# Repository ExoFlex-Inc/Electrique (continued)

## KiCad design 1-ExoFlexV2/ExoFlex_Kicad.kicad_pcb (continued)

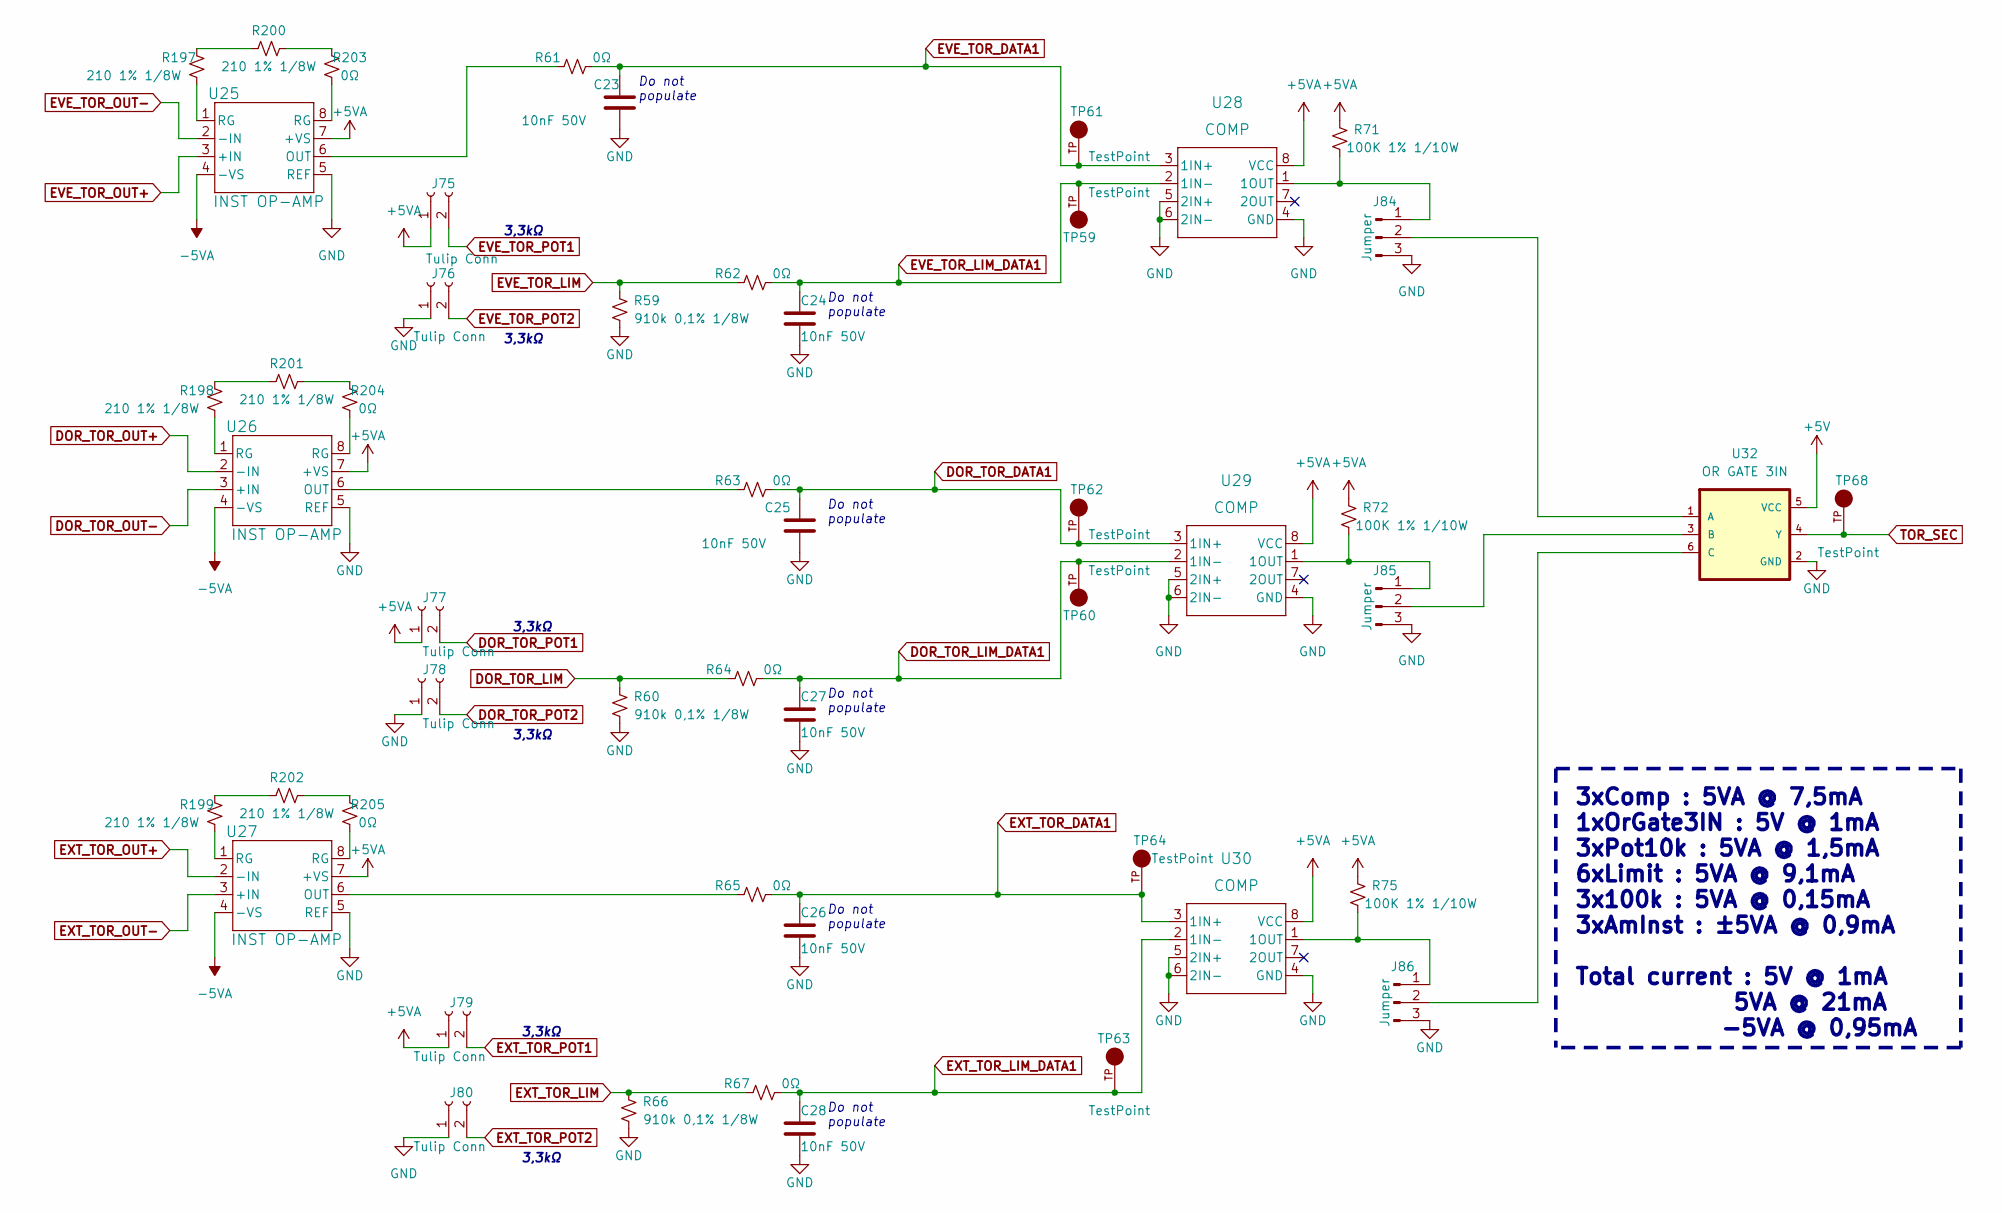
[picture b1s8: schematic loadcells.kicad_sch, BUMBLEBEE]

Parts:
C23, C24, C25, C26, C27, C28: 10nF 50V; C_0805_2012Metric; PART NUMBER GRM2195C1H103JA01D
J75, J76, J77, J78, J79, J80: Tulip Conn; PinSocket_1x02_P2.54mm_Vertical; PART NUMBER 801-87-002-10-001101
J84, J85, J86: Jumper; PinHeader_1x03_P2.54mm_Vertical; PART NUMBER 61300311121
R59, R60, R66: 910k 0,1% 1/8W; R_0805_2012Metric; PART NUMBER ERA-6AEB914V
R61, R62, R63, R64, R65, R67, R203, R204, R205: 0Ω; R_0805_2012Metric; PART NUMBER ERJ-6GEY0R00V
R71, R72, R75: 100K 1% 1/10W; R_0603_1608Metric; PART NUMBER ERJ-3EKF1003V
R197, R198, R199, R200, R201, R202: 210 1% 1/8W; R_0805_2012Metric; PART NUMBER ERJ-6ENF2100V
TP59, TP60, TP61, TP62, TP63, TP64, TP68: TestPoint; KEYSTONE_5005; PART NUMBER 5005
U25, U26, U27: INST OP-AMP; D0008A_SOIC_TEX; PART NUMBER INA823DR
U28, U29, U30: COMP; DGK8; PART NUMBER LM393DGKR
U32: OR GATE 3IN; SOT95P280X145-6N; PART NUMBER SN74LVC1G332DBVR

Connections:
+5V: U32.5 (VCC); also elsewhere on the board
+5VA: J75.1, J77.1, J79.1, R71.1, R72.1, R75.1, U25.7 (+VS), U26.7 (+VS), U27.7 (+VS), U28.8 (VCC), U29.8 (VCC), U30.8 (VCC); also elsewhere on the board
-5VA: U25.4 (-VS), U26.4 (-VS), U27.4 (-VS); also elsewhere on the board
DOR_TOR_DATA1: C25.1, R63.2, TP62.TP, U29.3 (1IN+); also elsewhere on the board
DOR_TOR_LIM: R60.1, R64.1; also elsewhere on the board
DOR_TOR_LIM_DATA1: C27.1, R64.2, TP60.TP, U29.2 (1IN-); also elsewhere on the board
DOR_TOR_OUT+: U26.2 (-IN); also elsewhere on the board
DOR_TOR_OUT-: U26.3 (+IN); also elsewhere on the board
DOR_TOR_POT1: J77.2; also elsewhere on the board
DOR_TOR_POT2: J78.2; also elsewhere on the board
EVE_TOR_DATA1: C23.1, R61.2, TP61.TP, U28.3 (1IN+); also elsewhere on the board
EVE_TOR_LIM: R59.1, R62.1; also elsewhere on the board
EVE_TOR_LIM_DATA1: C24.1, R62.2, TP59.TP, U28.2 (1IN-); also elsewhere on the board
EVE_TOR_OUT+: U25.3 (+IN); also elsewhere on the board
EVE_TOR_OUT-: U25.2 (-IN); also elsewhere on the board
EVE_TOR_POT1: J75.2; also elsewhere on the board
EVE_TOR_POT2: J76.2; also elsewhere on the board
EXT_TOR_DATA1: C26.1, R65.2, TP64.TP, U30.3 (1IN+); also elsewhere on the board
EXT_TOR_LIM: R66.1, R67.1; also elsewhere on the board
EXT_TOR_LIM_DATA1: C28.1, R67.2, TP63.TP, U30.2 (1IN-); also elsewhere on the board
EXT_TOR_OUT+: U27.2 (-IN); also elsewhere on the board
EXT_TOR_OUT-: U27.3 (+IN); also elsewhere on the board
EXT_TOR_POT1: J79.2; also elsewhere on the board
EXT_TOR_POT2: J80.2; also elsewhere on the board
GND: C23.2, C24.2, C25.2, C26.2, C27.2, C28.2, J76.1, J78.1, J80.1, J84.3, J85.3, J86.3, R59.2, R60.2, R66.2, U25.5 (REF), U26.5 (REF), U27.5 (REF), U28.4 (GND), U28.5 (2IN+), U28.6 (2IN-), U29.4 (GND), U29.5 (2IN+), U29.6 (2IN-), U30.4 (GND), U30.5 (2IN+), U30.6 (2IN-), U32.2 (GND); also elsewhere on the board
unnamed: J84.1, R71.2, U28.1 (1OUT)
unnamed: J84.2, U32.1 (A)
unnamed: J85.1, R72.2, U29.1 (1OUT)
unnamed: J85.2, U32.3 (B)
unnamed: J86.1, R75.2, U30.1 (1OUT)
unnamed: J86.2, U32.6 (C)
unnamed: R61.1, U25.6 (OUT)
unnamed: R63.1, U26.6 (OUT)
unnamed: R65.1, U27.6 (OUT)
unnamed: R197.1, U25.1 (RG)
unnamed: R197.2, R200.1
unnamed: R198.1, U26.1 (RG)
unnamed: R198.2, R201.1
unnamed: R199.1, U27.1 (RG)
unnamed: R199.2, R202.1
unnamed: R200.2, R203.1
unnamed: R201.2, R204.1
unnamed: R202.2, R205.1
unnamed: R203.2, U25.8 (RG)
unnamed: R204.2, U26.8 (RG)
unnamed: R205.2, U27.8 (RG)
TOR_SEC: TP68.TP, U32.4 (Y); also elsewhere on the board

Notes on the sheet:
3,3kΩ
Do not populate
3xComp : 5VA @ 7,5mA 1xOrGate3IN : 5V @ 1mA 3xPot10k : 5VA @ 1,5mA 6xLimit : 5VA @ 9,1mA 3x100k : 5VA @ 0,15mA 3xAmInst : ±5VA @ 0,9mA Total current : 5V @ 1mA 5VA @ 21mA -5VA @ 0,95mA

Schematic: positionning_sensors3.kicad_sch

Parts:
C50, C51, C52: 10nF 50V; C_0805_2012Metric; PART NUMBER GRM2195C1H103JA01D
J107, J108, J109: Jumper; PinHeader_1x03_P2.54mm_Vertical; PART NUMBER 61300311121
R155, R156, R157: 0Ω; R_0805_2012Metric; PART NUMBER ERJ-6GEY0R00V
R158, R159, R160, R161, R162, R163: 100K 1% 1/10W; R_0603_1608Metric; PART NUMBER ERJ-3EKF1003V
RV3, RV4, RV5: Trim 10k; TRIM_3362P-1-103LF; PART NUMBER 3362P-1-103LF
TP108, TP109, TP110, TP111, TP112, TP113, TP117: TestPoint; KEYSTONE_5005; PART NUMBER 5005
U58: Inverter; SN74LVC3G14DCUT; PART NUMBER SN74LVC3G14DCUT
U79, U80, U81: COMP; DGK8; PART NUMBER LM393DGKR
U82, U83: AND Gate; SOT95P270X145-5N; PART NUMBER SN74LVC1G08DBVR

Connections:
+5V: U58.8 (VCC), U82.5 (VCC), U83.5 (VCC); also elsewhere on the board
+5VA: R158.1, R159.1, R160.1, R161.2, R162.2, R163.2, RV3.2, RV4.3, RV5.3, U79.8 (VCC), U80.8 (VCC), U81.8 (VCC); also elsewhere on the board
FSR_POS1: R155.1; also elsewhere on the board
FSR_POS2: R156.1; also elsewhere on the board
FSR_POS3: R157.1; also elsewhere on the board
GND: C50.2, C51.2, C52.2, RV4.1, RV5.1, U58.3 (2A), U58.4 (GND), U58.6 (3A), U79.4 (GND), U79.5 (2IN+), U79.6 (2IN-), U80.4 (GND), U80.5 (2IN+), U80.6 (2IN-), U81.4 (GND), U81.5 (2IN+), U81.6 (2IN-), U82.3 (GND), U83.3 (GND); also elsewhere on the board
M_FSR_POS1: C50.1, R155.2, TP108.TP, U79.3 (1IN+); also elsewhere on the board
M_FSR_POS2: C51.1, R156.2, TP110.TP, U80.3 (1IN+); also elsewhere on the board
M_FSR_POS3: C52.1, R157.2, TP112.TP, U81.3 (1IN+); also elsewhere on the board
M_FSR_POS_LIM1: RV3.1, TP109.TP, U79.2 (1IN-); also elsewhere on the board
M_FSR_POS_LIM2: RV4.2, TP111.TP, U80.2 (1IN-); also elsewhere on the board
M_FSR_POS_LIM3: RV5.2, TP113.TP, U81.2 (1IN-); also elsewhere on the board
unnamed: J107.1, R158.2, U80.1 (1OUT)
unnamed: J107.2, U82.2 (B)
unnamed: J107.3, R161.1
unnamed: J108.1, R159.2, U79.1 (1OUT)
unnamed: J108.2, U82.1 (A)
unnamed: J108.3, R162.1
unnamed: J109.1, R160.2, U81.1 (1OUT)
unnamed: J109.2, U83.2 (B)
unnamed: J109.3, R163.1
unnamed: U58.1 (1A), U83.4 (Y)
unnamed: U82.4 (Y), U83.1 (A)
POS_FSR_SEC: TP117.TP, U58.7 (1Y); also elsewhere on the board

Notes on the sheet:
3xComp : 5VA @ 7,5mA 2xANDGate : 5V @ 2mA 1xNOTGte : 5V @ 1mA 3xPot10k : 5VA @ 1,5mA 6x100k : 5VA @ 0,3mA Total current : 5V @ 3,15mA 5VA @ 10mA
Do not populate

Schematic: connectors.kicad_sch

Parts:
D3, D4, D7, D8, D11, D13, D14, D17, D19, D21, D22, D23, D24, D25, D26, D27, D28, D29, D30, D31, D32, D33, D34, D35, D36, D37, D38, D109, D110, D111: TVS; DPY2_TEX; PART NUMBER TPD1E05U06DPYR
J13, J14, J15, J19, J20, J21, J22, J23, J24: 3POS; CON_39301039; PARTREV 03.03.2021
J16, J17, J18: 39281083; MOLEX_0039281083; PART NUMBER 0039281083
R113, R170, R171: 100K 1% 1/10W; R_0603_1608Metric; PART NUMBER ERJ-3EKF1003V

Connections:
+5VA: J13.3, J14.3, J15.3, J16.2, J17.2, J18.2, R113.2, R170.2, R171.2; also elsewhere on the board
-5VA: J16.4, J17.4, J18.4; also elsewhere on the board
DOR_AMP_LIM: D25.1 (K), J20.2; also elsewhere on the board
DOR_AMP_OUT: D8.1 (K), J14.2; also elsewhere on the board
DOR_AMP_POT1: D26.1 (K), J20.3; also elsewhere on the board
DOR_AMP_POT2: D24.1 (K), J20.1; also elsewhere on the board
DOR_TOR_INT: D110.1 (K), J17.1, R170.1; also elsewhere on the board
DOR_TOR_LIM: D34.1 (K), J23.2; also elsewhere on the board
DOR_TOR_OUT+: D14.1 (K), J17.3; also elsewhere on the board
DOR_TOR_OUT-: D11.1 (K), J17.5; also elsewhere on the board
DOR_TOR_POT1: D35.1 (K), J23.3; also elsewhere on the board
DOR_TOR_POT2: D33.1 (K), J23.1; also elsewhere on the board
EVE_AMP_LIM: D28.1 (K), J19.2; also elsewhere on the board
EVE_AMP_OUT: D13.1 (K), J13.2; also elsewhere on the board
EVE_AMP_POT1: D29.1 (K), J19.3; also elsewhere on the board
EVE_AMP_POT2: D27.1 (K), J19.1; also elsewhere on the board
EVE_TOR_INT: D111.1 (K), J16.1, R171.1; also elsewhere on the board
EVE_TOR_LIM: D37.1 (K), J22.2; also elsewhere on the board
EVE_TOR_OUT+: D19.1 (K), J16.3; also elsewhere on the board
EVE_TOR_OUT-: D17.1 (K), J16.5; also elsewhere on the board
EVE_TOR_POT1: D38.1 (K), J22.3; also elsewhere on the board
EVE_TOR_POT2: D36.1 (K), J22.1; also elsewhere on the board
EXT_AMP_LIM: D22.1 (K), J21.2; also elsewhere on the board
EXT_AMP_OUT: D3.1 (K), J15.2; also elsewhere on the board
EXT_AMP_POT1: D23.1 (K), J21.3; also elsewhere on the board
EXT_AMP_POT2: D21.1 (K), J21.1; also elsewhere on the board
EXT_TOR_INT: D109.1 (K), J18.1, R113.1; also elsewhere on the board
EXT_TOR_LIM: D31.1 (K), J24.2; also elsewhere on the board
EXT_TOR_OUT+: D7.1 (K), J18.3; also elsewhere on the board
EXT_TOR_OUT-: D4.1 (K), J18.5; also elsewhere on the board
EXT_TOR_POT1: D32.1 (K), J24.3; also elsewhere on the board
EXT_TOR_POT2: D30.1 (K), J24.1; also elsewhere on the board
GND: D3.2 (A), D4.2 (A), D7.2 (A), D8.2 (A), D11.2 (A), D13.2 (A), D14.2 (A), D17.2 (A), D19.2 (A), D21.2 (A), D22.2 (A), D23.2 (A), D24.2 (A), D25.2 (A), D26.2 (A), D27.2 (A), D28.2 (A), D29.2 (A), D30.2 (A), D31.2 (A), D32.2 (A), D33.2 (A), D34.2 (A), D35.2 (A), D36.2 (A), D37.2 (A), D38.2 (A), D109.2 (A), D110.2 (A), D111.2 (A), J13.1, J14.1, J15.1, J16.6, J16.7, J17.6, J17.7, J18.6, J18.7; also elsewhere on the board

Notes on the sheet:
3xMagEncoder : 5VA @ 19,5mA 3xTorSensor : ±5VA @ 42,85mA Total current : 5VA @ 65,47mA -5VA @ 45mA
Limite Torque Éversion
TORQUE
AMPLITUDE
- | | | | | | | | | | | | |Provient du ATO-STS-NJY65 | | | | | | | | | | | | -
Éversion
Extension
- | | | | | | |Provient du AS5600 | | | | | | -
Limite Amplitude Dorsiflexion
Limite Torque Dorsiflexion
Limite Amplitude Éversion
Dorsiflexion
Limite Amplitude Extension
Limite Torque Extension

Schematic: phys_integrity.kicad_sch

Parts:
J115, J116, J117: Jumper; PinHeader_1x03_P2.54mm_Vertical; PART NUMBER 61300311121
R173, R174, R175: 100K 1% 1/10W; R_0603_1608Metric; PART NUMBER ERJ-3EKF1003V
TP125: TestPoint; KEYSTONE_5005; PART NUMBER 5005
U53: OR GATE 3IN; SOT95P280X145-6N; PART NUMBER SN74LVC1G332DBVR

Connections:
+5V: R173.1, R174.1, R175.1, U53.5 (VCC); also elsewhere on the board
DOR_TOR_INT: J116.1, R174.2; also elsewhere on the board
EVE_TOR_INT: J117.1, R175.2; also elsewhere on the board
EXT_TOR_INT: J115.1, R173.2; also elsewhere on the board
GND: J115.3, J116.3, J117.3, U53.2 (GND); also elsewhere on the board
INT_SENSOR_SEC: TP125.TP, U53.4 (Y); also elsewhere on the board
unnamed: J115.2, U53.1 (A)
unnamed: J116.2, U53.3 (B)
unnamed: J117.2, U53.6 (C)

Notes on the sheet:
1xORGate3IN : 5V @ 0,01mA 12x100k : 5V @ 0,6mA Total current : 5V @ 1mA
NOTES:

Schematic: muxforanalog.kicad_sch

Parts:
J131, J132: Jumper; PinHeader_1x03_P2.54mm_Vertical; PART NUMBER 61300311121
R265, R266, R273, R274, R275, R276: 10K 1% 1/10W; R_0603_1608Metric; PART NUMBER ERJ-3EKF1002V
R267, R268, R269, R270: 3.3k 1% 1/8W; R_0805_2012Metric; PART NUMBER ERJ-6ENF3301V
R271, R272: 0Ω; R_0805_2012Metric; PART NUMBER ERJ-6GEY0R00V
R277, R278: 100k 1% 1/20W; R_0201_0603Metric; PART NUMBER ERJ-1GNF1003C
U56, U57: OP_AMP2; SOIC127P599X175-8N; PART NUMBER TL072IDR
U121, U122: MUX 8:1; SOT403-1_NXP; PART NUMBER 74HC4051PW,118

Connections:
+5V: U121.16 (VCC), U122.16 (VCC); also elsewhere on the board
+5VA: U56.8 (VCC+), U57.8 (VCC+); also elsewhere on the board
-5VA: U56.4 (VCC-), U57.4 (VCC-); also elsewhere on the board
ANA_DATA: J131.2; also elsewhere on the board
ANA_LIM_DATA: J132.2; also elsewhere on the board
ANA_S0: U121.11 (S0), U122.11 (S0); also elsewhere on the board
ANA_S1: U121.10 (S1), U122.10 (S1); also elsewhere on the board
ANA_S2: U121.9 (S2), U122.9 (S2); also elsewhere on the board
GND: R277.2, R278.2, U56.3 (1IN+), U56.5 (2IN+), U57.3 (1IN+), U57.5 (2IN+), U121.6 (E*), U121.7 (VEE), U121.8 (GND), U122.6 (E*), U122.7 (VEE), U122.8 (GND); also elsewhere on the board
M_FSR_POS1: U121.12 (Y3); also elsewhere on the board
M_FSR_POS2: U121.1 (Y4); also elsewhere on the board
M_FSR_POS3: U121.5 (Y5); also elsewhere on the board
M_FSR_POS_LIM1: U122.12 (Y3); also elsewhere on the board
M_FSR_POS_LIM2: U122.1 (Y4); also elsewhere on the board
M_FSR_POS_LIM3: U122.5 (Y5); also elsewhere on the board
M_LC_POS1: U121.13 (Y0); also elsewhere on the board
M_LC_POS2: U121.14 (Y1); also elsewhere on the board
M_LC_POS3: U121.15 (Y2); also elsewhere on the board
M_LC_POS_LIM1: U122.13 (Y0); also elsewhere on the board
M_LC_POS_LIM2: U122.14 (Y1); also elsewhere on the board
M_LC_POS_LIM3: U122.15 (Y2); also elsewhere on the board
M_TEMP_1: U121.2 (Y6); also elsewhere on the board
M_TEMP_2: U121.4 (Y7); also elsewhere on the board
M_TEMP_LIM1: U122.2 (Y6); also elsewhere on the board
M_TEMP_LIM2: U122.4 (Y7); also elsewhere on the board
unnamed: J131.1, R274.1, U56.7 (2OUT)
unnamed: J131.3, R277.1
unnamed: J132.1, R276.1, U57.7 (2OUT)
unnamed: J132.3, R278.1
unnamed: R265.1, U121.3 (Z)
unnamed: R265.2, R267.1, U56.2 (1IN-)
unnamed: R266.1, U122.3 (Z)
unnamed: R266.2, R268.1, U57.2 (1IN-)
unnamed: R267.2, R269.1
unnamed: R268.2, R270.1
unnamed: R269.2, R271.1
unnamed: R270.2, R272.1
unnamed: R271.2, R273.2, U56.1 (1OUT)
unnamed: R272.2, R275.2, U57.1 (1OUT)
unnamed: R273.1, R274.2, U56.6 (2IN-)
unnamed: R275.1, R276.2, U57.6 (2IN-)

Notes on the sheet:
2xMUX8_1 : 5V @ 100mA 2xOP : 5VA @ 5mA Total current : 5V @ 110mA

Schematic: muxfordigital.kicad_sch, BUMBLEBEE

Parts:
TP128: TestPoint; KEYSTONE_5005; PART NUMBER 5005
U12, U13: MUX 8:1; SOT403-1_NXP; PART NUMBER 74HC4051PW,118
U59: Inverter; SN74LVC3G14DCUT; PART NUMBER SN74LVC3G14DCUT

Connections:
+5V: U12.16 (VCC), U13.16 (VCC), U59.8 (VCC); also elsewhere on the board
GND: U12.7 (VEE), U12.8 (GND), U13.1 (Y4), U13.2 (Y6), U13.4 (Y7), U13.5 (Y5), U13.7 (VEE), U13.8 (GND), U59.3 (2A), U59.4 (GND), U59.6 (3A); also elsewhere on the board
INT_POS_SEC: U13.15 (Y2); also elsewhere on the board
INT_PROX_SEC: U13.12 (Y3); also elsewhere on the board
INT_SENSOR_SEC: U13.14 (Y1); also elsewhere on the board
M_BUT_POS1: U12.2 (Y6); also elsewhere on the board
M_BUT_POS2: U12.4 (Y7); also elsewhere on the board
M_BUT_POS3: U13.13 (Y0); also elsewhere on the board
M_BUT_PROX_L1: U12.13 (Y0); also elsewhere on the board
M_BUT_PROX_L2: U12.14 (Y1); also elsewhere on the board
M_BUT_PROX_R1: U12.15 (Y2); also elsewhere on the board
M_BUT_PROX_R2: U12.12 (Y3); also elsewhere on the board
M_REC_PROX1: U12.1 (Y4); also elsewhere on the board
M_REC_PROX2: U12.5 (Y5); also elsewhere on the board
unnamed: U13.6 (E*), U59.7 (1Y)
SW&INT: TP128.TP, U12.3 (Z), U13.3 (Z); also elsewhere on the board
SW&INT_SG0: U12.11 (S0), U13.11 (S0); also elsewhere on the board
SW&INT_SG1: U12.10 (S1), U13.10 (S1); also elsewhere on the board
SW&INT_SG2: U12.9 (S2), U13.9 (S2); also elsewhere on the board
SW&INT_SG3: U12.6 (E*), U59.1 (1A); also elsewhere on the board

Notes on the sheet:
2xMUX8_1 : 5V @ 100mA Total current : 5V @ 106mA

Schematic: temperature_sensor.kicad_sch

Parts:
C53, C54: 10nF 50V; C_0805_2012Metric; PART NUMBER GRM2195C1H103JA01D
J110, J111: Jumper; PinHeader_1x03_P2.54mm_Vertical; PART NUMBER 61300311121
R164, R165: 0Ω; R_0805_2012Metric; PART NUMBER ERJ-6GEY0R00V
R166, R167: 100K 1% 1/10W; R_0603_1608Metric; PART NUMBER ERJ-3EKF1003V
RV6, RV7: Trim 10k; TRIM_3362P-1-103LF; PART NUMBER 3362P-1-103LF
TP118, TP119, TP120, TP121, TP124: TestPoint; KEYSTONE_5005; PART NUMBER 5005
U50: OR GATE 3IN; SOT95P280X145-6N; PART NUMBER SN74LVC1G332DBVR
U85, U86: COMP; DGK8; PART NUMBER LM393DGKR

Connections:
+5V: U50.5 (VCC); also elsewhere on the board
+5VA: R166.1, R167.1, RV6.3, RV7.3, U85.8 (VCC), U86.8 (VCC); also elsewhere on the board
GND: C53.2, C54.2, J110.3, J111.3, RV6.1, RV7.1, U50.2 (GND), U50.6 (C), U85.4 (GND), U85.5 (2IN+), U85.6 (2IN-), U86.4 (GND), U86.5 (2IN+), U86.6 (2IN-); also elsewhere on the board
M_TEMP_1: C53.1, R164.2, TP118.TP, U86.3 (1IN+); also elsewhere on the board
M_TEMP_2: C54.1, R165.2, TP120.TP, U85.3 (1IN+); also elsewhere on the board
M_TEMP_LIM1: RV6.2, TP119.TP, U86.2 (1IN-); also elsewhere on the board
M_TEMP_LIM2: RV7.2, TP121.TP, U85.2 (1IN-); also elsewhere on the board
unnamed: J110.1, R167.2, U86.1 (1OUT)
unnamed: J110.2, U50.1 (A)
unnamed: J111.1, R166.2, U85.1 (1OUT)
unnamed: J111.2, U50.3 (B)
TEMP_OUT_1: R164.1; also elsewhere on the board
TEMP_OUT_2: R165.1; also elsewhere on the board
TEMP_SEC: TP124.TP, U50.4 (Y); also elsewhere on the board

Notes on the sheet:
Do not populate
2xComp : 5VA @ 5mA 2xORGate : 5V @ 2mA 2xPot10k : 5VA @ 1mA 2x100k : 5VA @ 0,1mA Total current : 5V @ 2,1mA 5VA @ 6,5mA

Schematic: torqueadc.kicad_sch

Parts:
J68, J69, J70, J87, J88, J89: Jumper; PinHeader_1x03_P2.54mm_Vertical; PART NUMBER 61300311121
R89, R225, R228: 100k 1% 1/8W; R_0805_2012Metric; PART NUMBER ERJ-6ENF1003V
R206, R207, R208, R215, R216, R217, R218, R219, R220, R221, R233, R234, R235, R236, R237, R238, R239, R240, R241, R242, R243, R245, R246, R247, R248, R249, R259, R260, R261, R262: 10K 1% 1/10W; R_0603_1608Metric; PART NUMBER ERJ-3EKF1002V
R209, R210, R211, R222, R231, R250, R251, R255, R256: 3.3k 1% 1/8W; R_0805_2012Metric; PART NUMBER ERJ-6ENF3301V
R212, R213, R214, R224, R227, R230, R232, R257, R258: 0Ω; R_0805_2012Metric; PART NUMBER ERJ-6GEY0R00V
R223, R226, R229: 200k 1% 1/8W; R_0805_2012Metric; PART NUMBER ERJ-6ENF2003V
R244, R252, R253, R254, R263, R264: 100k 1% 1/20W; R_0201_0603Metric; PART NUMBER ERJ-1GNF1003C
TP11, TP12, TP13, TP15, TP16, TP81: TestPoint; KEYSTONE_5005; PART NUMBER 5005
U33, U34, U35, U36, U37, U38, U39, U40, U41: OP_AMP2; SOIC127P599X175-8N; PART NUMBER TL072IDR

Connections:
+5VA: R223.2, R226.2, R229.2, U33.8 (VCC+), U34.8 (VCC+), U35.8 (VCC+), U36.8 (VCC+), U37.8 (VCC+), U38.8 (VCC+), U39.8 (VCC+), U40.8 (VCC+), U41.8 (VCC+); also elsewhere on the board
-5VA: U33.4 (VCC-), U34.4 (VCC-), U35.4 (VCC-), U36.4 (VCC-), U37.4 (VCC-), U38.4 (VCC-), U39.4 (VCC-), U40.4 (VCC-), U41.4 (VCC-); also elsewhere on the board
DOR_TOR_DATA: J88.2; also elsewhere on the board
DOR_TOR_DATA1: R206.1; also elsewhere on the board
DOR_TOR_LIM_DATA: J70.2; also elsewhere on the board
DOR_TOR_LIM_DATA1: R249.1; also elsewhere on the board
EVE_TOR_DATA: J89.2; also elsewhere on the board
EVE_TOR_DATA1: R208.1; also elsewhere on the board
EVE_TOR_LIM_DATA: J69.2; also elsewhere on the board
EVE_TOR_LIM_DATA1: R248.1; also elsewhere on the board
EXT_TOR_DATA: J87.2; also elsewhere on the board
EXT_TOR_DATA1: R207.1; also elsewhere on the board
EXT_TOR_LIM_DATA: J68.2; also elsewhere on the board
EXT_TOR_LIM_DATA1: R215.1; also elsewhere on the board
GND: R89.1, R225.1, R228.1, R244.2, R252.2, R253.2, R254.2, R263.2, R264.2, U33.3 (1IN+), U33.5 (2IN+), U34.3 (1IN+), U34.5 (2IN+), U35.3 (1IN+), U35.5 (2IN+), U36.3 (1IN+), U36.5 (2IN+), U37.3 (1IN+), U38.3 (1IN+), U39.3 (1IN+), U40.3 (1IN+), U40.5 (2IN+), U41.3 (1IN+), U41.5 (2IN+); also elsewhere on the board
unnamed: J68.1, R240.1, U36.7 (2OUT)
unnamed: J68.3, R244.1
unnamed: J69.1, R260.1, U40.7 (2OUT)
unnamed: J69.3, R263.1
unnamed: J70.1, R262.1, U41.7 (2OUT)
unnamed: J70.3, R264.1
unnamed: J87.1, R247.2, U39.1 (1OUT)
unnamed: J87.3, R254.1
unnamed: J88.1, R246.2, U38.1 (1OUT)
unnamed: J88.3, R253.1
unnamed: J89.1, R245.2, U37.1 (1OUT)
unnamed: J89.3, R252.1
unnamed: R206.2, R211.1, U33.2 (1IN-)
unnamed: R207.2, R209.1, U34.2 (1IN-)
unnamed: R208.2, R210.1, U35.2 (1IN-)
unnamed: R209.2, R214.1
unnamed: R210.2, R212.1
unnamed: R211.2, R213.1
unnamed: R212.2, R220.2, TP12.TP, U35.1 (1OUT)
unnamed: R213.2, R216.2, TP13.TP, U33.1 (1OUT)
unnamed: R214.2, R218.2, TP11.TP, U34.1 (1OUT)
unnamed: R215.2, R222.1, U36.2 (1IN-)
unnamed: R216.1, R217.2, U33.6 (2IN-)
unnamed: R217.1, R235.1, TP16.TP, U33.7 (2OUT)
unnamed: R218.1, R219.2, U34.6 (2IN-)
unnamed: R219.1, R233.1, TP81.TP, U34.7 (2OUT)
unnamed: R220.1, R221.2, U35.6 (2IN-)
unnamed: R221.1, R234.1, TP15.TP, U35.7 (2OUT)
unnamed: R222.2, R231.1
unnamed: R223.1, R224.2
unnamed: R224.1, R225.2, R237.1
unnamed: R226.1, R227.2
unnamed: R227.1, R228.2, R238.1
unnamed: R229.1, R230.2
unnamed: R89.2, R230.1, R236.1
unnamed: R231.2, R232.1
unnamed: R232.2, R239.2, U36.1 (1OUT)
unnamed: R233.2, R238.2, R243.1
unnamed: R234.2, R236.2, R241.1
unnamed: R235.2, R237.2, R242.1
unnamed: R239.1, R240.2, U36.6 (2IN-)
unnamed: R241.2, R245.1, U37.2 (1IN-)
unnamed: R242.2, R246.1, U38.2 (1IN-)
unnamed: R243.2, R247.1, U39.2 (1IN-)
unnamed: R248.2, R250.1, U40.2 (1IN-)
unnamed: R249.2, R251.1, U41.2 (1IN-)
unnamed: R250.2, R255.1
unnamed: R251.2, R256.1
unnamed: R255.2, R257.1
unnamed: R256.2, R258.1
unnamed: R257.2, R259.2, U40.1 (1OUT)
unnamed: R258.2, R261.2, U41.1 (1OUT)
unnamed: R259.1, R260.2, U40.6 (2IN-)
unnamed: R261.1, R262.2, U41.6 (2IN-)

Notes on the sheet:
0-3,3V
-3,3-0V
±1,65V(+)
±1,65V(-)
0-5V
NOTES:
±5V
12xOP : 5VA @ 37,5mA 3x300k : 5VA @ 0,06mA Total current : 5VA @ 40mA
Topologie (gauche) : - Atténuateur pour passer de ±5V à ±1,65V - Gain négatif pour inverser le signal de l'atténuateur (Ampli-OP inverseur) - Sommateur pour faire un offset de 1,65V et avoir 0-3,3V Topologie (gauche) : - Atténuateur pour passer de 0-5V à -3,3-0V - Gain négatif pour inverser le sign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

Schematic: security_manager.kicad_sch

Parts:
NT13: NetTie_2; NetTie-2_THT_Pad0.3mm
TP24: TestPoint; KEYSTONE_5005; PART NUMBER 5005
U8, U9: OR Gate 8; D14; PART NUMBER CD4078BM96
U15: OR GATE 3IN; SOT95P280X145-6N; PART NUMBER SN74LVC1G332DBVR

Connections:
+5V: U8.14 (VDD), U9.14 (VDD), U15.5 (VCC); also elsewhere on the board
ALIM_SEC: NT13.2, TP24.TP, U15.4 (Y); also elsewhere on the board
AMP_SEC: U8.5 (D); also elsewhere on the board
GND: U8.7 (VSS), U9.7 (VSS), U9.10 (F), U9.11 (G), U9.12 (H), U15.2 (GND), U15.6 (C); also elsewhere on the board
INT_POS_SEC: U8.10 (F); also elsewhere on the board
INT_PROX_SEC: U8.11 (G); also elsewhere on the board
INT_SENSOR_SEC: U8.12 (H); also elsewhere on the board
LEFTRIGHT_SEC: U9.2 (A); also elsewhere on the board
MAX_SW_SEC: U9.3 (B); also elsewhere on the board
unnamed: U8.1 (AK), U15.1 (A)
unnamed: U9.1 (AK), U15.3 (B)
POS_BUT_SEC: U9.4 (C); also elsewhere on the board
POS_FSR_SEC: U8.3 (B); also elsewhere on the board
POS_LC_SEC: U8.4 (C); also elsewhere on the board
PROX_BUT_SEC: U9.5 (D); also elsewhere on the board
PROX_OPTO_SEC: U9.9 (E); also elsewhere on the board
TEMP_SEC: U8.2 (A); also elsewhere on the board
TOR_SEC: U8.9 (E); also elsewhere on the board
URG_SEC: NT13.1; also elsewhere on the board

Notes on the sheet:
1xOrGate3IN : 5V @ 0,01mA 2xORGate8CH : 5V @ 2mA Total current : 5V @ 3mA
Notes :

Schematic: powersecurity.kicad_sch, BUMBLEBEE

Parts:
C1: 10uF 10V X7R; C_0805_2012Metric; PART NUMBER GRM21BR71A106KA73L
C2: 220uF 20% 50V; CAP_EEHZS1H221P; PART NUMBER EEH-ZS1H221P
D1, D2: SHOTT 30V 12A; DIO_SS12P2L-M3_86A; PART NUMBER SS12P3L-M3/86A
D115: LED; WL-SMCW_0603; PART NUMBER 150060RS75000
F1: Fuse; 696108003002; PART NUMBER 696108003002
J1, J3, J4: 14 AWG; PHOENIX_1755736; PART NUMBER 1755736
J2: Jumper; PinHeader_1x03_P2.54mm_Vertical; PART NUMBER 61300311121
K1: Relay; UD2_NU_KEM-L; PART NUMBER UD2-5NU
Q1: MOSFET 20V 200mA; DIO_RB558WMF_ROM; PART NUMBER RE1C002UNTCL
R1, R4: 10K 1% 1/10W; R_0603_1608Metric; PART NUMBER ERJ-3EKF1002V
R2: 5.1K 1% 1/10W; R_0603_1608Metric; PART NUMBER ERJ-3EKF5101V
R184: 2,2k 1% 1/2W; R_0805_2012Metric; PART NUMBER ERJ-P06F2201V
TP1, TP2, TP3, TP4, TP5: TestPoint; KEYSTONE_5005; PART NUMBER 5005
U1: TVS 24V; SOT-23-3_DBZ_TEX; PART NUMBER TSM36ADBZR
U2: Shott 100V; D2PAK_STM; PART NUMBER STPS20M100SG-TR
U3: Inverter; SN74LVC3G14DCUT; PART NUMBER SN74LVC3G14DCUT
U4: SR-Latch; CD4044BPWR; PART NUMBER CD4044BPWR

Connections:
+5V: D1.3, K1.8, U3.8 (VCC), U4.5 (ENABLE), U4.16 (VDD); also elsewhere on the board
+24V: J2.1, K1.3; also elsewhere on the board
ALIM_SEC: U4.3 (S1); also elsewhere on the board
GND: C1.2, C2.2, D2.1, D2.2, D115.1 (K), J1.2, J3.2, J4.2, Q1.2 (S), R1.2, R4.2, U1.1 (GND), U1.2 (GND), U2.1, U2.2, U3.3 (2A), U3.4 (GND), U3.6 (3A), U4.8 (VSS); also elsewhere on the board
unnamed: C1.1, R2.2, U3.1 (1A)
unnamed: C2.1, F1.2, J2.2, R184.2, TP2.TP, U1.3 (IO), U2.3
unnamed: D1.1, D1.2, J4.1, K1.1, Q1.3 (D), TP4.TP
unnamed: D2.3, J3.1, K1.2, TP3.TP
unnamed: D115.2 (A), R184.1
unnamed: F1.1, J1.1
unnamed: Q1.1 (G), R4.1, TP5.TP, U4.13 (Q1)
unnamed: TP1.TP, U3.7 (1Y), U4.4 (R1)
RESET: R1.1, R2.1; also elsewhere on the board

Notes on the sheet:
Contacteur ouvert = moteur activé Sortie 5V et 24V pour PCB 48V externe futur
Notes :
24V
Vers contacteur 24V
OutPut 5V sécurité
Contacteur : 24V @ 100mA CoilRelais : 5V @ 20mA FreeWheel5V : 5V @ 2mA FreeWheel24V : 24V @ 4,16mA Latch : 5V @ 1mA Total Current : 5V @ 25,2 mA 24V @ 109,37mA

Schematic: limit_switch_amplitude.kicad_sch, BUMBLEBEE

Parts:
C29, C30, C31, C32, C33, C34, C35: 10uF 10V X7R; C_0805_2012Metric; PART NUMBER GRM21BR71A106KA73L
J90, J91, J92: Jumper; PinHeader_1x03_P2.54mm_Vertical; PART NUMBER 61300311121
R98, R99, R100, R101, R102, R103, R110: 10K 1% 1/10W; R_0603_1608Metric; PART NUMBER ERJ-3EKF1002V
R104, R105, R106, R107, R108, R109, R111: 5.1K 1% 1/10W; R_0603_1608Metric; PART NUMBER ERJ-3EKF5101V
TP84: TestPoint; KEYSTONE_5005; PART NUMBER 5005
U11, U42, U43: Inverter; SN74LVC3G14DCUT; PART NUMBER SN74LVC3G14DCUT
U49: OR GATE 3IN; SOT95P280X145-6N; PART NUMBER SN74LVC1G332DBVR

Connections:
+5V: U11.8 (VCC), U42.8 (VCC), U43.8 (VCC), U49.5 (VCC); also elsewhere on the board
GND: C29.2, C30.2, C31.2, C32.2, C33.2, C34.2, C35.2, J90.3, J91.3, J92.3, R98.2, R99.2, R100.2, R101.2, R102.2, R103.2, R110.2, U11.4 (GND), U42.4 (GND), U43.3 (2A), U43.4 (GND), U43.6 (3A), U49.2 (GND); also elsewhere on the board
MAX_SW_1: R99.1, R104.1; also elsewhere on the board
MAX_SW_2: R98.1, R105.1; also elsewhere on the board
MAX_SW_3: R100.1, R106.1; also elsewhere on the board
MAX_SW_SEC: TP84.TP, U49.4 (Y); also elsewhere on the board
MIN_SW_1: R101.1, R107.1; also elsewhere on the board
MIN_SW_2: R102.1, R108.1; also elsewhere on the board
MIN_SW_3: R103.1, R109.1; also elsewhere on the board
unnamed: C29.1, R104.2, U11.1 (1A)
unnamed: C30.1, R105.2, U11.3 (2A)
unnamed: C31.1, R106.2, U11.6 (3A)
unnamed: C32.1, R107.2, U42.1 (1A)
unnamed: C33.1, R108.2, U42.3 (2A)
unnamed: C34.1, R109.2, U42.6 (3A)
unnamed: C35.1, R111.2, U43.1 (1A)
unnamed: J90.1, U11.2 (3Y)
unnamed: J91.1, U11.7 (1Y)
unnamed: J92.1, U11.5 (2Y)
SWMAX1: J91.2, U49.1 (A); also elsewhere on the board
SWMAX2: J92.2, U49.3 (B); also elsewhere on the board
SWMAX3: J90.2, U49.6 (C); also elsewhere on the board
SWMIN1: U42.7 (1Y); also elsewhere on the board
SWMIN2: U42.5 (2Y); also elsewhere on the board
SWMIN3: U42.2 (3Y); also elsewhere on the board
URG_SEC: U43.7 (1Y); also elsewhere on the board
URG_USER: R110.1, R111.1; also elsewhere on the board

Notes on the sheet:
Debouncing
2xOrGate : 5V @ 1mA 3x100k : 5V @ 0,15mA Total current : 5V @ 2mA

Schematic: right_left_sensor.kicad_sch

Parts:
C36, C37: 10uF 10V X7R; C_0805_2012Metric; PART NUMBER GRM21BR71A106KA73L
J93, J94: Jumper; PinHeader_1x03_P2.54mm_Vertical; PART NUMBER 61300311121
R115, R116: 10K 1% 1/10W; R_0603_1608Metric; PART NUMBER ERJ-3EKF1002V
R117, R118: 5.1K 1% 1/10W; R_0603_1608Metric; PART NUMBER ERJ-3EKF5101V
TP85: TestPoint; KEYSTONE_5005; PART NUMBER 5005
U10: XNOR Gate; SC-74A_SOT753_NEX; PART NUMBER 74LV1T87GVH
U44: Inverter; SN74LVC3G14DCUT; PART NUMBER SN74LVC3G14DCUT

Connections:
+5V: U10.5 (VCC), U44.8 (VCC); also elsewhere on the board
GND: C36.2, C37.2, J93.3, J94.3, R115.2, R116.2, U10.3 (GND), U44.4 (GND), U44.6 (3A); also elsewhere on the board
LEFTRIGHT_SEC: TP85.TP, U10.4 (Y); also elsewhere on the board
MAX_SW_4: R115.1, R117.1; also elsewhere on the board
MAX_SW_5: R116.1, R118.1; also elsewhere on the board
unnamed: C36.1, R117.2, U44.1 (1A)
unnamed: C37.1, R118.2, U44.3 (2A)
unnamed: J93.1, U44.7 (1Y)
unnamed: J94.1, U44.5 (2Y)
SWMAX4: J93.2, U10.1 (B); also elsewhere on the board
SWMAX5: J94.2, U10.2 (A); also elsewhere on the board

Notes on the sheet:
Debouncing
1xXNORGate : 5V @ 50mA 2xNOTGate : 5V @ 2mA Total current : 5V @ 55mA

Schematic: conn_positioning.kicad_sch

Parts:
D79, D80, D81, D85, D86, D87, D91, D92, D93, D94, D95, D96, D112, D113, D114: TVS; DPY2_TEX; PART NUMBER TPD1E05U06DPYR
J43, J44, J45: 5POS; CON_39302050; PART NUMBER 39302050
J46, J47, J48: 2POS; CON_39281023; PART NUMBER 0039281023
J49, J50, J51: 4POS; CON_39301049; PARTREV 03.03.2021
R29, R30, R31: 1K 1% 1/10W; R_0603_1608Metric; PART NUMBER ERJ-3EKF1001V
R32, R33, R34, R172, R182, R183: 100K 1% 1/10W; R_0603_1608Metric; PART NUMBER ERJ-3EKF1003V
R169, R176, R177: 5.1K 1% 1/10W; R_0603_1608Metric; PART NUMBER ERJ-3EKF5101V

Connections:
+5V: R29.2, R30.2, R31.2; also elsewhere on the board
+5VA: J43.2, J44.2, J45.2, J49.3, J50.3, J51.3, R32.1, R33.1, R34.1, R172.1, R182.1, R183.1; also elsewhere on the board
BUT_POS1: D85.1 (K), J46.2; also elsewhere on the board
BUT_POS2: D86.1 (K), J47.2; also elsewhere on the board
BUT_POS3: D87.1 (K), J48.2; also elsewhere on the board
FSR_POS1: D94.1 (K), J49.2, R176.2; also elsewhere on the board
FSR_POS1_INT: D93.1 (K), J49.4, R32.2; also elsewhere on the board
FSR_POS2: D95.1 (K), J50.2, R177.2; also elsewhere on the board
FSR_POS2_INT: D91.1 (K), J50.4, R33.2; also elsewhere on the board
FSR_POS3: D96.1 (K), J51.2, R169.2; also elsewhere on the board
FSR_POS3_INT: D92.1 (K), J51.4, R34.2; also elsewhere on the board
GND: D79.2 (A), D80.2 (A), D81.2 (A), D85.2 (A), D86.2 (A), D87.2 (A), D91.2 (A), D92.2 (A), D93.2 (A), D94.2 (A), D95.2 (A), D96.2 (A), D112.2 (A), D113.2 (A), D114.2 (A), J43.4, J43.5, J44.4, J44.5, J45.4, J45.5, J49.1, J50.1, J51.1, R169.1, R176.1, R177.1; also elsewhere on the board
LC_POS1: D79.1 (K), J43.3; also elsewhere on the board
LC_POS1_INT: D112.1 (K), J43.1, R172.2; also elsewhere on the board
LC_POS2: D80.1 (K), J44.3; also elsewhere on the board
LC_POS2_INT: D113.1 (K), J44.1, R182.2; also elsewhere on the board
LC_POS3: D81.1 (K), J45.3; also elsewhere on the board
LC_POS3_INT: D114.1 (K), J45.1, R183.2; also elsewhere on the board
unnamed: J46.1, R29.1
unnamed: J47.1, R30.1
unnamed: J48.1, R31.1

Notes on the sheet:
But Pos 2
LC Pos 3
But Pos 3
FSR 1
3xRes1k : 5V @ 15mA 3xRes100k : 5VA @ 0,3mA 3xLC : 5VA @ 15,6mA Total current : 5V @ 15,75mA 5VA @ 17mA
FSR 3
FSR 2
LC Pos 2
But Pos 1
LC Pos 1

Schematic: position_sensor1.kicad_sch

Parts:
C44, C45, C46: 10nF 50V; C_0805_2012Metric; PART NUMBER GRM2195C1H103JA01D
J101, J102, J103: Jumper; PinHeader_1x03_P2.54mm_Vertical; PART NUMBER 61300311121
R137, R138, R139: 0Ω; R_0805_2012Metric; PART NUMBER ERJ-6GEY0R00V
R140, R141, R142, R143, R144, R145: 100K 1% 1/10W; R_0603_1608Metric; PART NUMBER ERJ-3EKF1003V
RV1, RV2, RV27: Trim 10k; TRIM_3362P-1-103LF; PART NUMBER 3362P-1-103LF
TP94, TP95, TP96, TP97, TP98, TP99, TP103: TestPoint; KEYSTONE_5005; PART NUMBER 5005
U48: Inverter; SN74LVC3G14DCUT; PART NUMBER SN74LVC3G14DCUT
U67, U68, U69: COMP; DGK8; PART NUMBER LM393DGKR
U70, U71: AND Gate; SOT95P270X145-5N; PART NUMBER SN74LVC1G08DBVR

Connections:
+5V: U48.8 (VCC), U70.5 (VCC), U71.5 (VCC); also elsewhere on the board
+5VA: R140.1, R141.1, R142.1, R143.2, R144.2, R145.2, RV1.3, RV2.3, RV27.3, U67.8 (VCC), U68.8 (VCC), U69.8 (VCC); also elsewhere on the board
GND: C44.2, C45.2, C46.2, RV1.1, RV2.1, RV27.1, U48.3 (2A), U48.4 (GND), U48.6 (3A), U67.4 (GND), U67.5 (2IN+), U67.6 (2IN-), U68.4 (GND), U68.5 (2IN+), U68.6 (2IN-), U69.4 (GND), U69.5 (2IN+), U69.6 (2IN-), U70.3 (GND), U71.3 (GND); also elsewhere on the board
LC_POS1: R137.1; also elsewhere on the board
LC_POS2: R138.1; also elsewhere on the board
LC_POS3: R139.1; also elsewhere on the board
M_LC_POS1: C44.1, R137.2, TP94.TP, U67.3 (1IN+); also elsewhere on the board
M_LC_POS2: C45.1, R138.2, TP96.TP, U68.3 (1IN+); also elsewhere on the board
M_LC_POS3: C46.1, R139.2, TP98.TP, U69.3 (1IN+); also elsewhere on the board
M_LC_POS_LIM1: RV27.2, TP95.TP, U67.2 (1IN-); also elsewhere on the board
M_LC_POS_LIM2: RV1.2, TP97.TP, U68.2 (1IN-); also elsewhere on the board
M_LC_POS_LIM3: RV2.2, TP99.TP, U69.2 (1IN-); also elsewhere on the board
unnamed: J101.1, R140.2, U68.1 (1OUT)
unnamed: J101.2, U70.2 (B)
unnamed: J101.3, R143.1
unnamed: J102.1, R141.2, U67.1 (1OUT)
unnamed: J102.2, U70.1 (A)
unnamed: J102.3, R144.1
unnamed: J103.1, R142.2, U69.1 (1OUT)
unnamed: J103.2, U71.2 (B)
unnamed: J103.3, R145.1
unnamed: U48.1 (1A), U71.4 (Y)
unnamed: U70.4 (Y), U71.1 (A)
POS_LC_SEC: TP103.TP, U48.7 (1Y); also elsewhere on the board

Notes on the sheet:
Do not populate
3xComp : 5VA @ 7,5mA 2xANDGate : 5V @ 2mA 1xNOTGate : 5V @ 1mA 3xPot10k : 5VA @ 1,5mA 6x100k : 5VA @ 0,3mA Total current : 5V @ 3,15mA 5VA @ 10mA
